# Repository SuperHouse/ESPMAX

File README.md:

ESP Max Prototyping Board
=========================

Copyright 2016 SuperHouse Automation Pty Ltd www.superhouse.tv  

Prototyping board for IoT projects using the ESP8266 microcontroller
on the ESP-12E module.

Features:

 * CP2102 USB-to-Serial converter.
 * 12 digital I/O channels at 3.3V.
 * 1 analog input with 0-3.2V range.
 * Power from USB or DC IN
 * 5V and 3.3V voltage regulators.
 * Jumper to select power source.
 * Prototyping area.
 * Expansion headers in D1 Mini format to suit expansion shields.

More information is available at:

  http://www.superhouse.tv/espmax

INSTALLATION
------------
The design is saved as an EAGLE project. EAGLE PCB design software is
available from www.cadsoftusa.com free for non-commercial use. To use
this project download it and place the directory containing these files
into the "eagle" directory on your computer.

DISTRIBUTION
------------
The specific terms of distribution of this project are governed by the
license referenced below.

LICENSE
-------
Licensed under the TAPR Open Hardware License (www.tapr.org/OHL).
The "license" folder within this repository also contains a copy of
this license in plain text format.

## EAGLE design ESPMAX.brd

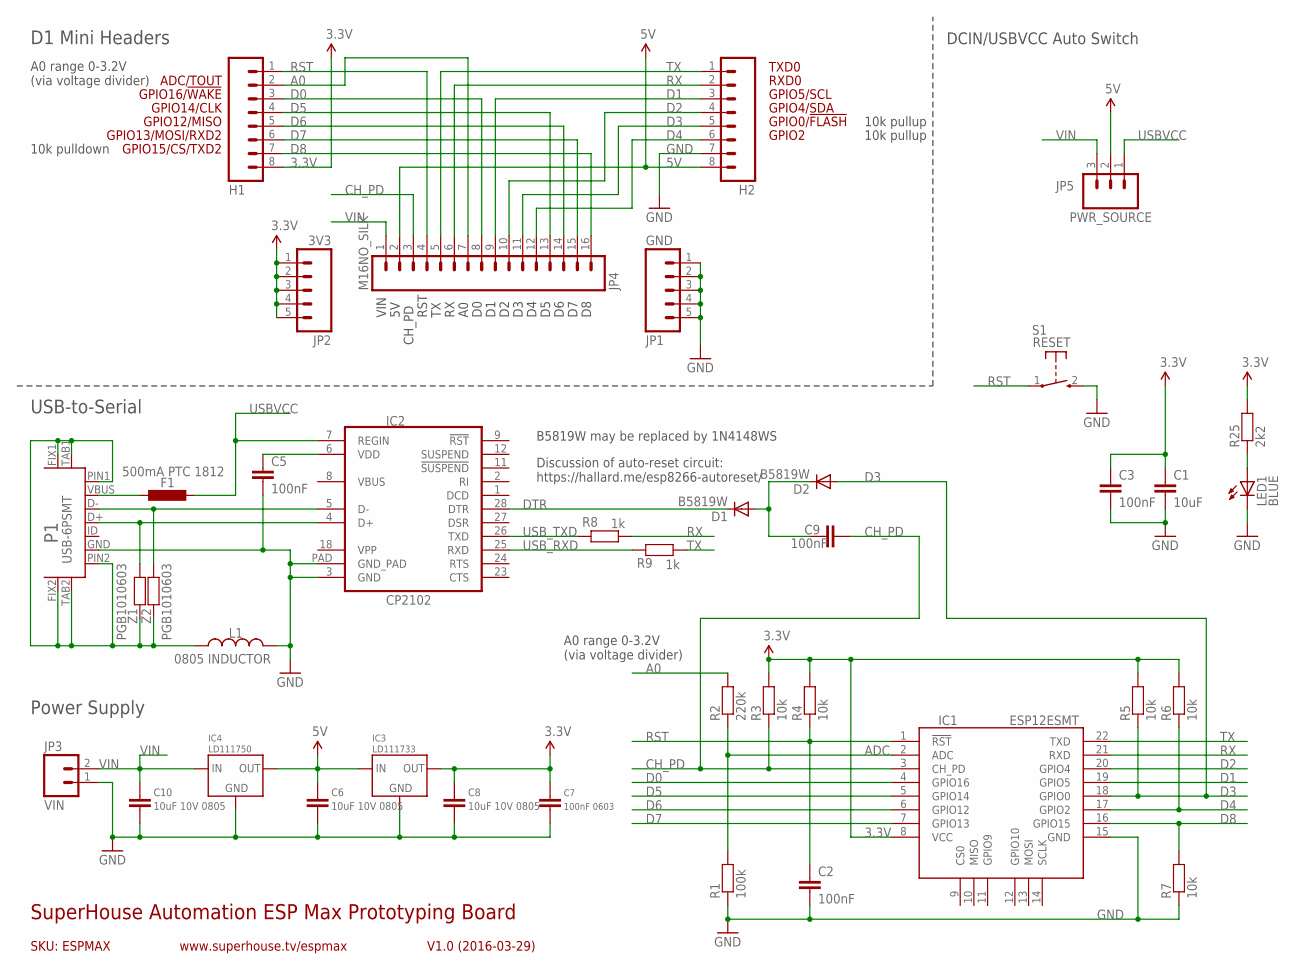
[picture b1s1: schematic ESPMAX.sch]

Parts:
C1: 10uF; 0805
C2, C3, C5, C9: 100nF; 0603
C6, C8, C10: 10uF 10V 0805; C0805
C7: 100nF 0603; 0603
D1, D2: B5819W; SOD-323
F1: 500mA PTC 1812; L1812
H1, H2: M08; 1X08
IC1: ESP12ESMT; ESP12E
IC2: CP2102; QFN-28
IC3: LD111733; SOT-223
IC4: LD111750; SOT-223
JP1: GND; 1X05_NO_SILK
JP2: 3V3; 1X05_NO_SILK
JP3: VIN; SCREWTERMINAL-3.5MM-2
JP4: M16NO_SILK; 1X16_NO_SILK
JP5: PWR_SOURCE; 1X03
L1: 0805 INDUCTOR; 0805-LARGE
LED1: BLUE; LED-0603
P1: USB-6PSMT; USB-MICROB-MB05PMXX
R1: 100k; 0603
R2: 220k; 0603
R3, R4, R5, R6, R7: 10k; 0603
R8, R9: 1k; 0603
R25: 2k2; 0603
S1: RESET; TACTILE_SWITCH_SMD_2PIN_TINY
Z1, Z2: PGB1010603; 0603

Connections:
3.3V: C1.1, C3.1, C7.1, C8.1, H1.8, IC1.8 (VCC), IC3.2 (OUT), IC3.4 (OUT), JP2.1, JP2.2, JP2.3, JP2.4, JP2.5, R3.2, R4.2, R5.2, R6.2, R25.2
5V: C6.1, H2.8, IC3.3 (IN), IC4.2 (OUT), IC4.4 (OUT), JP4.2, JP5.2
A0: H1.2, JP4.7, R2.2
ADC: IC1.2 (ADC), R1.2, R2.1
CH_PD: C9.2, IC1.3 (CH_PD), JP4.3, R3.1
D0: H1.3, IC1.4 (GPIO16), JP4.8
D1: H2.3, IC1.19 (GPIO5), JP4.9
D2: H2.4, IC1.20 (GPIO4), JP4.10
D3: D2.2 (A), H2.5, IC1.18 (GPIO0), JP4.11, R5.1
D4: H2.6, IC1.17 (GPIO2), JP4.12, R6.1
D5: H1.4, IC1.5 (GPIO14), JP4.13
D6: H1.5, IC1.6 (GPIO12), JP4.14
D7: H1.6, IC1.7 (GPIO13), JP4.15
D8: H1.7, IC1.16 (GPIO15), JP4.16, R7.2
DTR: D1.1 (C), IC2.28 (DTR)
GND: C1.2, C2.2, C3.2, C5.2, C6.2, C7.2, C8.2, C10.2, H2.7, IC1.15 (GND), IC2.3 (GND), IC2.PAD (GND_PAD), IC3.1 (GND), IC4.1 (GND), JP1.1, JP1.2, JP1.3, JP1.4, JP1.5, JP3.1, L1.2, LED1.C, P1.GND, R1.1, R7.1, S1.2 (S)
unnamed: LED1.A, R25.1
unnamed: C9.1, D1.2 (A), D2.1 (C)
unnamed: L1.1, P1.FIX1, P1.FIX2, P1.PIN1, P1.PIN2, P1.TAB1, P1.TAB2, Z1.2, Z2.2
unnamed: IC2.4 (D+), P1.D+, Z1.1
unnamed: IC2.5 (D-), P1.D-, Z2.1
unnamed: C5.1, IC2.6 (VDD)
unnamed: F1.1, P1.VBUS
RST: C2.1, H1.1, IC1.1 (!RST), JP4.4, R4.1, S1.1
RX: H2.2, IC1.21 (RXD), JP4.6, R8.1
TX: H2.1, IC1.22 (TXD), JP4.5, R9.1
USBVCC: F1.2, IC2.7 (REGIN), JP5.1
USB_RXD: IC2.25 (RXD), R9.2
USB_TXD: IC2.26 (TXD), R8.2
VIN: C10.1, IC4.3 (IN), JP3.2, JP4.1, JP5.3

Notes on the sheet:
SKU: ESPMAX
SuperHouse Automation ESP Max Prototyping Board
V1.0 (2016-03-29)
www.superhouse.tv/espmax
D1 Mini Headers
GPIO2
GPIO0/!FLASH
GPIO12/MISO
GPIO4/SDA
GPIO5/SCL
RXD0
TXD0
GPIO13/MOSI/RXD2
GPIO14/CLK
GPIO15/CS/TXD2
GPIO16/!WAKE
ADC/TOUT
10k pulldown
10k pullup
RST
Discussion of auto-reset circuit: https://hallard.me/esp8266-autoreset/
VIN
CH_PD
A0 range 0-3.2V (via voltage divider)
USB-to-Serial
Power Supply
B5819W may be replaced by 1N4148WS
DCIN/USBVCC Auto Switch

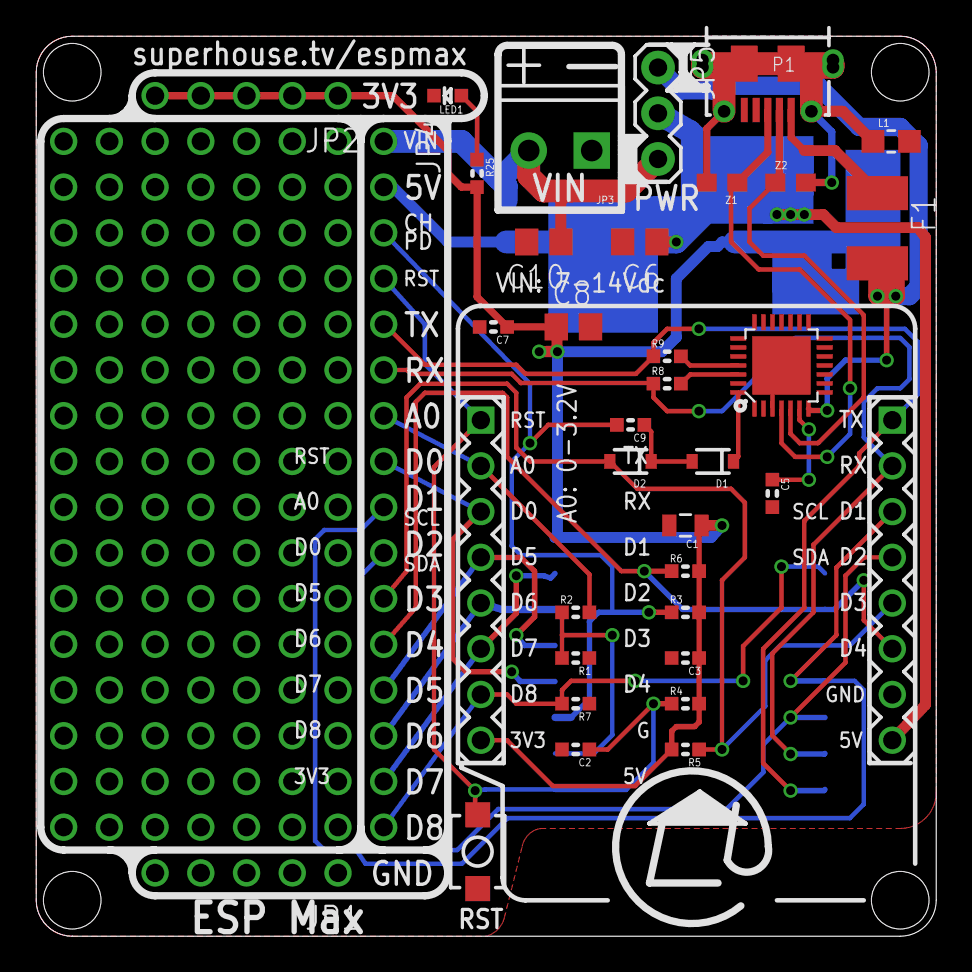
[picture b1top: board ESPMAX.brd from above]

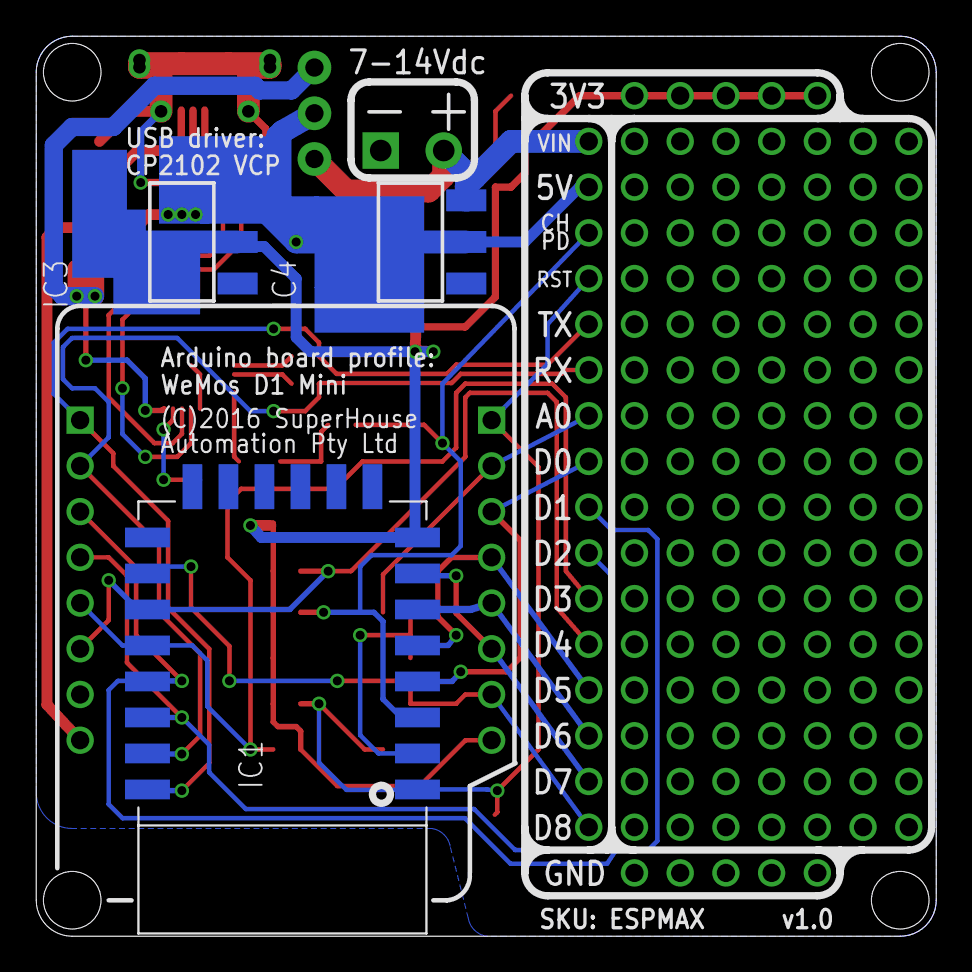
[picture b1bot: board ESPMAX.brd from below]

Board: 2 copper layers, 50.0 x 50.0 mm, 39 parts (3 on the bottom side), 30 nets.

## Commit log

2016-03-29 Initial import
2018-03-28 Minor silkscreen improvements
2020-08-10 Updated Eagle file format

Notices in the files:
ESPMAX.brd:
(C)2016 SuperHouse
parts and their libraries:
freetronics-original: Licensing: CC v3.0 Share-Alike You are welcome to use this library for commercial purposes.
